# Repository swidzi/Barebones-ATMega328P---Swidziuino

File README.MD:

This barebones Arduino/Atmega328 is made as a proof of concept for a 3018Pro CNC Mill.
This design has been milled, but NOT TESTED!

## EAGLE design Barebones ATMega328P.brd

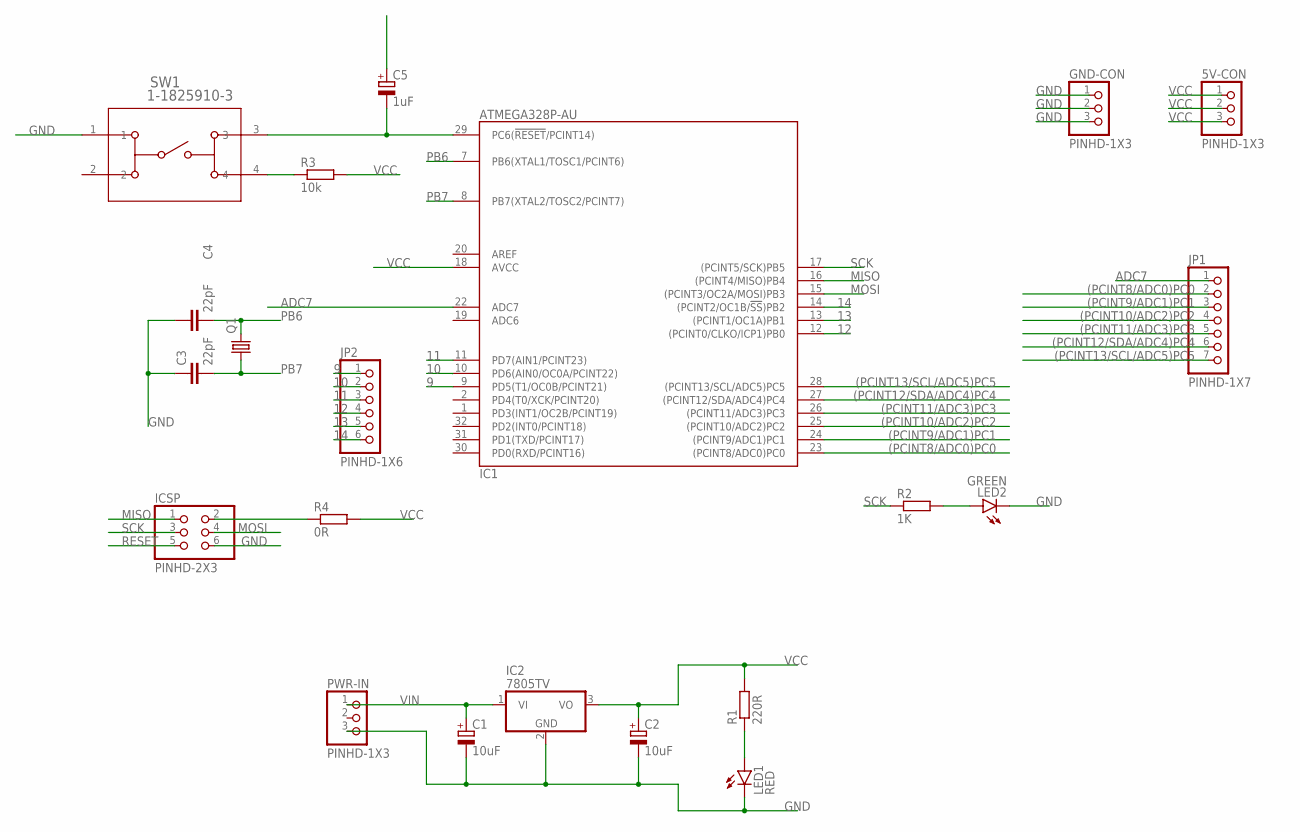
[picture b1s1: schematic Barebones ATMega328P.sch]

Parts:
5V-CON: PINHD-1X3; 1X03
C1, C2: 10uF; E5-8,5
C3, C4: 22pF; C025-025X050
C5: 1uF; E5-8,5
GND-CON: PINHD-1X3; 1X03
IC1: ATMEGA328P-AU; QFP32_7X7_0.80
IC2: 7805TV; TO220V
ICSP: PINHD-2X3; 2X03
JP1: PINHD-1X7; 1X07
JP2: PINHD-1X6; 1X06
LED1: RED; LED3MM
LED2: GREEN; LED3MM
PWR-IN: PINHD-1X3; 1X03
Q1: CRYSTALHC49S; HC49/S
R1: 220R; 0207/10
R2: 1K; 0207/10
R3: 10k; 0207/10
R4: 0R; 0207/10
SW1: 1-1825910-3; SW4_1825910-D

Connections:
9: IC1.9 (PD5(T1/OC0B/PCINT21)), JP2.1
10: IC1.10 (PD6(AIN0/OC0A/PCINT22)), JP2.2
11: IC1.11 (PD7(AIN1/PCINT23)), JP2.3
12: IC1.12 ((PCINT0/CLKO/ICP1)PB0), JP2.4
13: IC1.13 ((PCINT1/OC1A)PB1), JP2.5
14: IC1.14 ((PCINT2/OC1B/!SS!)PB2), JP2.6
(PCINT8/ADC0)PC0: IC1.23 ((PCINT8/ADC0)PC0), JP1.2
(PCINT9/ADC1)PC1: IC1.24 ((PCINT9/ADC1)PC1), JP1.3
(PCINT10/ADC2)PC2: IC1.25 ((PCINT10/ADC2)PC2), JP1.4
(PCINT11/ADC3)PC3: IC1.26 ((PCINT11/ADC3)PC3), JP1.5
(PCINT12/SDA/ADC4)PC4: IC1.27 ((PCINT12/SDA/ADC4)PC4), JP1.6
(PCINT13/SCL/ADC5)PC5: IC1.28 ((PCINT13/SCL/ADC5)PC5), JP1.7
ADC7: IC1.22 (ADC7), JP1.1
GND: C1.-, C2.-, C3.1, C4.1, GND-CON.1, GND-CON.2, GND-CON.3, IC1.3 (GND), IC1.5 (GND), IC1.21 (GND), IC2.2 (GND), ICSP.6, LED1.K (C), LED2.K (C), PWR-IN.3, SW1.1
MISO: IC1.16 ((PCINT4/MISO)PB4), ICSP.1
MOSI: IC1.15 ((PCINT3/OC2A/MOSI)PB3), ICSP.4
unnamed: LED1.A, R1.1
unnamed: R3.1, SW1.4
unnamed: C5.-, IC1.29 (PC6(!RESET!/PCINT14)), SW1.3
unnamed: ICSP.2, R4.1
unnamed: LED2.A, R2.2
PB6: C4.2, IC1.7 (PB6(XTAL1/TOSC1/PCINT6)), Q1.2
PB7: C3.2, IC1.8 (PB7(XTAL2/TOSC2/PCINT7)), Q1.1
RESET: C5.+, ICSP.5
SCK: IC1.17 ((PCINT5/SCK)PB5), ICSP.3, R2.1
VCC: 5V-CON.1, 5V-CON.2, 5V-CON.3, C2.+, IC1.4 (VCC), IC1.6 (VCC), IC1.18 (AVCC), IC2.3 (VO), R1.2, R3.2, R4.2
VIN: C1.+, IC2.1 (VI), PWR-IN.1

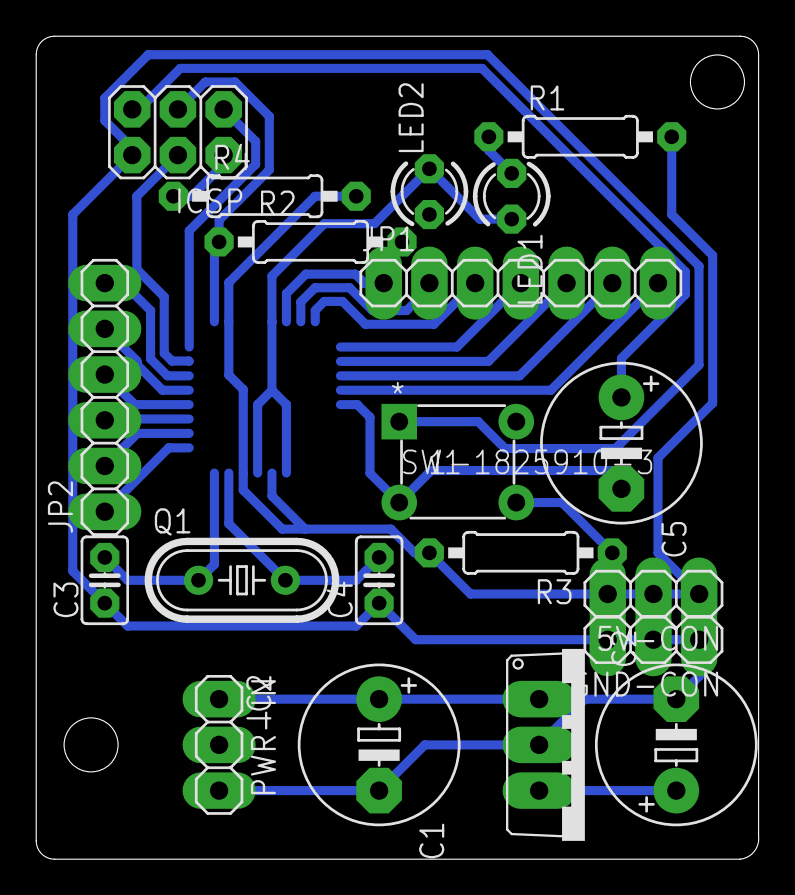
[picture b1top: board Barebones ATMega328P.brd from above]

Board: 2 copper layers, 40.1 x 45.7 mm, 21 parts (1 on the bottom side), 27 nets.

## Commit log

2021-01-12 Initial version
2021-01-12 v. 0.9
2021-01-12 Moved Power LED, made board footprint smaller
2021-01-18 Added README.MD
2021-01-18 Create LICENSE

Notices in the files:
parts and their libraries:
COPYRIGHT: Copyright (C) 2016 Accelerated Designs. All rights reserved
